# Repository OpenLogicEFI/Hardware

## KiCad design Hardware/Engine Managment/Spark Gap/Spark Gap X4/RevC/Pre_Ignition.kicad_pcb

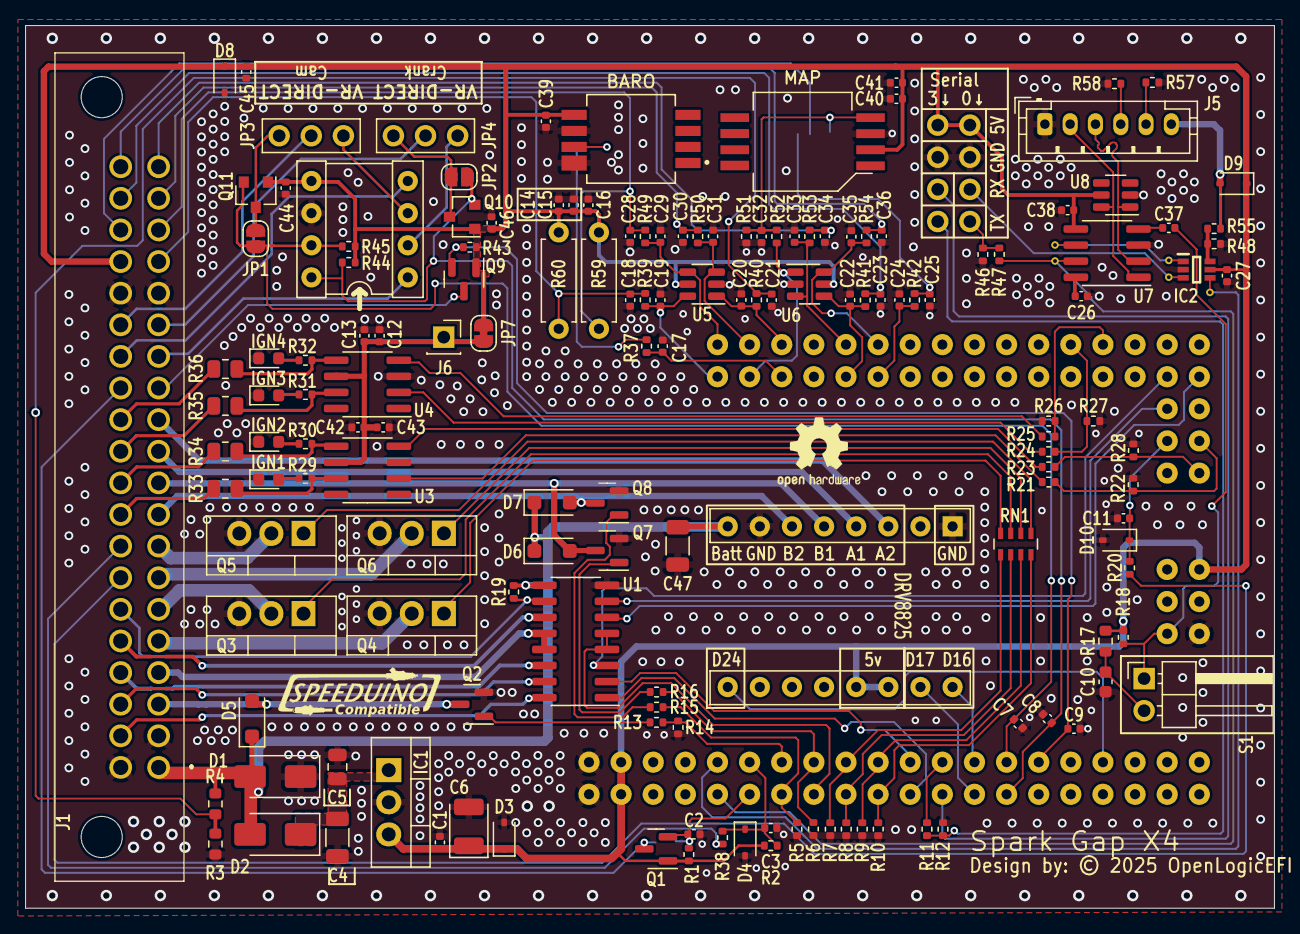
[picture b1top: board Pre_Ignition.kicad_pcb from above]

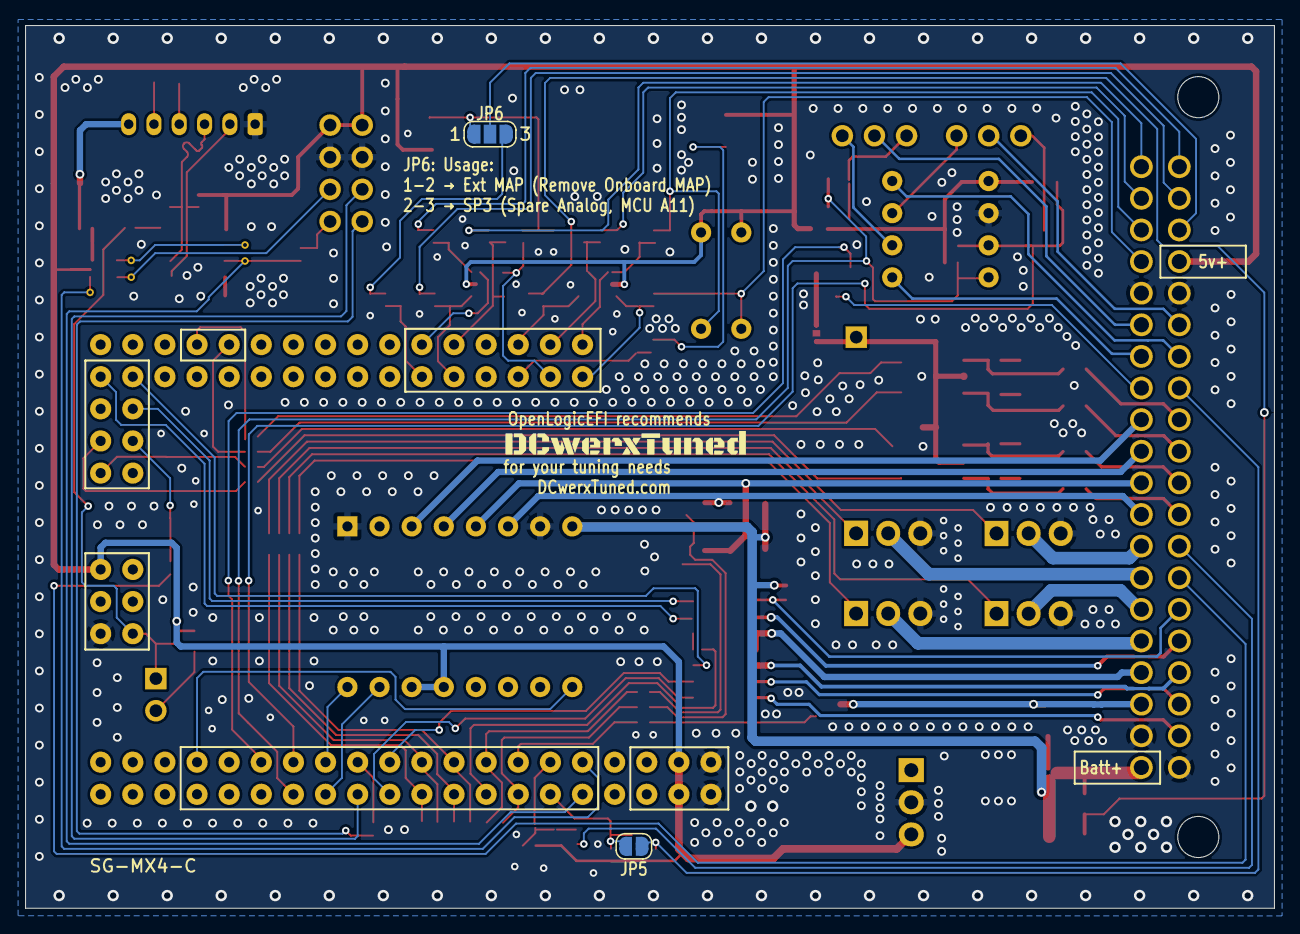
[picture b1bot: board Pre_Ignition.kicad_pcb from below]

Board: 2 copper layers, 98.8 x 69.8 mm, 166 parts (2 on the bottom side), 120 nets.

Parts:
A1: DRV8825_Module; DVR8825-Labeled-Front
C1, C7, C12, C14, C17, C18, C21, C23, C25, C26, C27, C28, C30, C34, C36, C37, C38, C39, C40, C43, C44, C45, C46: 100nF; C_0402_1005Metric
C2, C8, C9: 10nF; C_0402_1005Metric
C3, C11, C15, C19, C20, C22, C24, C29, C31, C33, C35: 220nF; C_0402_1005Metric
C4, C47: 10uF; C_1206_3216Metric
C5: 470nF; C_0805_2012Metric
C6: 100uF; CP_EIA-3528-15_AVX-H
C10: 10uF; C_0603_1608Metric
C13, C16, C41, C42: 1uF; C_0402_1005Metric
C32: 47pF; C_0402_1005Metric
D1: SMAJ18CA; D_SMA
D2: SS34; D_SMA
D3, D4, D8, D10: 5.6v; D_SOD-323
D5, D6, D7: DSK210; D_SOD-123F
D9: 1N5819WS; D_SOD-323
G1: Logo_Open_Hardware_Small; SpeeduinoCompatible-14mm
G2: Logo_Open_Hardware_Small; OSHW-Logo2_7.3x6mm_SilkScreen
IC1: 7805; TO-220-3_Vertical_SmallCrtYrd
IC2: 74LVC1G157GW,125; SOP65P210X110-6N
IC3: KP234XTMA1; KP234-Handsoldering
IC4: MPXHZ6400; MPXHxxx_Handsoldering
IGN1, IGN2, IGN3, IGN4: LED; LED_0603_1608Metric
J1: MX23A40NF1
J2: VR_Header; Socket_VRConditioner_Corrected
J3, J4: Conn_01x04; 1X4-PROTO-NoSilk
J5: USB-S0; JST_PH_B6B-PH-K_1x06_P2.00mm_Vertical
J6: Conn_01x01; PinSocket_1x01_P2.54mm_Vertical
JP1, JP2, JP5: FET Bypass; SolderJumper-2_P1.3mm_Open_RoundedPad1.0x1.5mm
JP3, JP4: DIRECT/VR; 1x03-Proto
JP6: SolderJumper_3_Open; SolderJumper-3-OPEN
JP7: Conn_01x02; SolderJumper-2_P1.3mm_Bridged_RoundedPad1.0x1.5mm
Q1, Q2, Q7, Q8, Q9, Q10, Q11: AO3400A; SOT-23
Q3, Q4, Q5, Q6: STP75N04Z; TO-220-3_Vertical
R1, R11, R20, R21, R23, R24, R25, R43, R44, R45, R47: 1k; R_0402_1005Metric
R2: 2.2k; R_0402_1005Metric
R3: 1k; R_0603_1608Metric
R4: 3.9k; R_0603_1608Metric
R5, R6, R7, R8, R9, R10, R14, R22, R26, R27, R28: 100k; R_0402_1005Metric
R12, R46: 2k; R_0402_1005Metric
R13, R15, R16, R29, R30, R31, R32, R38, R39, R40, R41, R42, R49, R50, R52, R53, R54, R55: 470r; R_0402_1005Metric
R17: 120r; R_0603_1608Metric
R18, R19, R48: 10k; R_0402_1005Metric
R33, R34, R35, R36: 22; R_0805_2012Metric
R37, R51: 51k; R_0402_1005Metric
R57, R58: 5.1k; R_0402_1005Metric
R59, R60: 2.49k; R_Axial_DIN0207_L6.3mm_D2.5mm_P7.62mm_Horizontal
RN1: RN_1k; R_Array_Concave_4x0603
S1: Reset Control; PinHeader_1x02_P2.54mm_Horizontal
TP1, TP2, TP3, TP4, TP5: TestPoint; TestPoint_THT_D0.6mm_Drill0.3mm
U1: ULN2003ADR; SOIC-16_3.9x9.9mm_P1.27mm
U2: Mega_Pro_VinPinsUnpopulated; Arduino_Mega_Mini_2560_SmallCrtYd_NoVin
U3, U4: TC4424; SOIC-8_3.9x4.9mm_P1.27mm
U5, U6, U8: SRV05-4; SOT-23-6
U7: CH340N; SOIC-8_3.9x4.9mm_P1.27mm

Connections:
+5V: A1.13 (~RST), A1.14 (~SLP), C1.1, C6.1, C14.1, C15.1, C16.1, C27.2, C38.1, C39.1, C40.1, C41.1, C44.1, C45.1, C46.1, D3.1 (K), D8.1 (K), D9.1 (K), IC1.3 (OUT), IC2.5 (VCC), IC3.5 (VDD), IC4.2 (VS), J1.37, J2.5, J3.1, J4.1, JP7.2 (B), Q1.1 (G), Q9.1 (G), Q10.1 (G), Q11.1 (G), R1.1, R2.2, R17.2, R18.1, R43.1, R44.1, R45.1, R59.1, R60.2, U2.5V_1 (5V), U2.5V_2 (5V), U2.5V_3 (5V), U5.5 (REF), U6.5 (REF), U7.5 (VCC), U8.5 (REF)
+BATT: A1.8 (VMOT), C47.1, D1.2 (A2), D2.2 (A), D5.1 (K), D6.1 (K), D7.1 (K), J1.1, R4.2, R19.2, U1.9 (COM)
+VSW: C12.1, C13.1, C42.1, C43.1, J6.1, JP7.1 (A), U3.6 (V+), U4.6 (V+)
/MCU and Power/Batt_Protected: C4.1, C5.1, D2.1 (K), IC1.1 (IN)
ADC1: C23.1, J1.39, R41.2
ADC2: C36.1, J1.40, R54.2
ADC3: C25.1, JP6.3 (B), R42.2
BOOST: J1.4, U1.12 (O5), U1.13 (O4)
BaroIn: IC3.7 (VOUT), R37.1
CH340-TX0: IC2.1 (I1), TP4.1, TP5.1, U7.6 (RXD)
CLT: C18.1, J1.17, R39.2, R60.1
Cam2: J1.33, JP5.1 (A), Q1.3 (D)
Cam-In: J1.35, JP3.2
Clutch: J1.27, R20.2
Crank-In: J1.15, JP4.2
D12-OUT: J1.23, U1.15 (O2)
D13-OUT: J1.22, U1.16 (O1)
D+: J5.2, U7.1 (UD+), U8.6 (I/O_4)
D-: J5.3, U7.2 (UD-), U8.1 (I/O_1)
Fan: J1.25, U1.11 (O6)
Flex: J1.28, R38.2
Fuel-Pump: J1.24, U1.14 (O3)
GND: A1.1 (GND), A1.7 (GND), C1.2, C2.1, C3.2, C4.2, C5.2, C6.2, C7.1, C8.1, C9.2, C10.2, C11.2, C12.2, C13.2, C14.2, C15.2, C16.2, C17.2, C18.2, C19.2, C20.2, C21.2, C22.2, C23.2, C24.2, C25.2, C26.2, C27.1, C28.2, C29.2, C30.2, C31.2, C32.2, C33.2, C34.2, C35.2, C36.2, C38.2, C39.2, C40.2, C41.2, C42.2, C43.2, C44.2, C45.2, C46.2, C47.2, D1.1 (A1), D3.2 (A), D4.2 (A), D8.2 (A), D10.2 (A), IC1.2 (GND), IC2.2 (GND), IC3.6 (GND), IC3.8 (GND), IC4.3 (GND), IGN1.1 (K), IGN2.1 (K), IGN3.1 (K), IGN4.1 (K), J1.2, J1.16, J1.21, J1.36, J2.6, J3.2, J4.2, J5.1, Q2.2 (S), Q3.3 (S), Q4.3 (S), Q5.3 (S), Q6.3 (S), Q7.2 (S), Q8.2 (S), R3.1, R5.1, R6.1, R7.1, R8.1, R9.1, R10.1, R12.2, R14.1, R22.1, R26.1, R27.1, R28.1, R46.2, R48.1, R51.1, R57.2, R58.2, U1.8 (GND), U2.GND_1 (GND), U2.GND_2 (GND), U2.GND_3 (GND), U3.3 (GND), U4.3 (GND), U5.2 (GND), U6.2 (GND), U7.3 (GND), U8.2 (GND)
IAT: C28.1, J1.18, R49.2, R59.2
IDLE1: A1.6 (B2), D7.2 (A), J1.9, Q8.3 (D)
IDLE2: A1.5 (B1), D6.2 (A), J1.10, Q7.3 (D)
IGN1: J1.32, R36.1
IGN2: J1.31, R35.1
IGN3: J1.30, R34.1
IGN4: J1.29, R33.1
INJ1: J1.5, Q4.2 (D)
INJ2: J1.6, Q3.2 (D)
INJ3: J1.7, Q6.2 (D)
INJ4: J1.8, Q5.2 (D)
MC-A0: C29.1, R49.1, U2.A0, U5.4 (I/O_3)
MC-A1: C19.1, R39.1, U2.A1, U5.6 (I/O_4)
MC-A2: C31.1, R50.1, U2.A2, U5.3 (I/O_2)
MC-A3: R52.2, U2.A3, U6.1 (I/O_1)
MC-A4: C20.1, R40.1, U2.A4, U5.1 (I/O_1)
MC-A5: C17.1, R37.2, U2.A5
MC-A8: C33.1, R53.1, U2.A8, U6.3 (I/O_2)
MC-A9: C22.1, R41.1, U2.A9, U6.4 (I/O_3)
MC-A10: C35.1, R54.1, U2.A10, U6.6 (I/O_4)
MC-A11: C24.1, R42.1, U2.A11
MC-D2: C3.1, D4.1 (K), R2.1, R38.1, U2.D2
MC-D3: C2.2, JP5.2 (B), Q1.2 (S), R1.2, U2.D3
MC-D4: R13.1, R14.2, U2.D4
MC-D5: R5.2, R15.1, U2.D5
MC-D6: R6.2, R16.1, U2.D6
MC-D7: U1.4 (I4), U1.5 (I5), U2.D7
MC-D8: R7.2, RN1.5 (R4.2), U2.D8
MC-D9: R8.2, RN1.6 (R3.2), U2.D9
MC-D10: R9.2, RN1.7 (R2.2), U2.D10
MC-D11: R10.2, RN1.8 (R1.2), U2.D11
MC-D12: U1.2 (I2), U2.D12
MC-D13: U1.1 (I1), U2.D13
MC-D14-TX3: R11.1, U2.D14
MC-D15-RX3: J3.3, U2.D15
MC-D16: A1.16 (DIR), U2.D16
MC-D17: A1.15 (STEP), U2.D17
MC-D18: C7.2, J2.7, JP1.2 (B), Q11.2 (S), R45.2, U2.D18
MC-D19: C8.2, J2.8, JP2.2 (B), Q10.2 (S), R44.2, U2.D19
MC-D20: C9.1, Q9.2 (S), R43.2, U2.D20
MC-D24: A1.9 (~EN), U2.D24
MC-D38: R24.1, R27.2, U2.D38
MC-D40: R25.1, R26.2, U2.D40
MC-D45: U1.3 (I3), U2.D45
MC-D47: U1.6 (I6), U2.D47
MC-D49: U1.7 (I7), U2.D49
MC-D50: R21.1, R22.2, U2.D50
MC-D51: C11.1, D10.1 (K), R20.1, U2.D51
MC-D52: R23.1, R28.2, U2.D52
MC-RESET: C37.2, R18.2, S1.1, U2.RESET
MC-RX0: IC2.4 (Y), TP1.1, U2.RX
MC-TX0: R47.1, TP3.1, U2.TX, U7.7 (TXD)
Map-Ext: J1.38, JP6.2 (C)
MapIn: C32.1, IC4.4 (VOUT), JP6.1 (A), R51.2, R52.1
unnamed: C21.1, R3.2, R4.1, R40.2
unnamed: IC2.6 (S), R48.2, R55.1
unnamed: IGN1.2 (A), R29.2
unnamed: IGN2.2 (A), R30.2
unnamed: IGN3.2 (A), R31.2
unnamed: IGN4.2 (A), R32.2
unnamed: J3.4, R11.2, R12.1
unnamed: J4.4, R46.1, R47.2
unnamed: J5.4, R58.1
unnamed: J5.5, R57.1
unnamed: JP1.1 (A), JP3.1, Q11.3 (D)
unnamed: JP2.1 (A), JP4.1, Q10.3 (D)
unnamed: Q2.1 (G), R13.2
unnamed: Q3.1 (G), RN1.3 (R3.1)
unnamed: Q4.1 (G), RN1.4 (R4.1)
unnamed: Q5.1 (G), RN1.1 (R1.1)
unnamed: Q6.1 (G), RN1.2 (R2.1)
unnamed: Q7.1 (G), R16.2
unnamed: Q8.1 (G), R15.2
unnamed: C10.1, R17.1, S1.2
unnamed: R21.2, U3.2 (IN_A)
unnamed: R23.2, U3.4 (IN_B)
unnamed: R29.1, R33.2, U3.7 (OUT_A)
unnamed: R30.1, R34.2, U3.5 (OUT_B)
unnamed: R24.2, U4.2 (IN_A)
unnamed: R25.2, U4.4 (IN_B)
unnamed: R31.1, R35.2, U4.7 (OUT_A)
unnamed: R32.1, R36.2, U4.5 (OUT_B)
unnamed: C26.1, U7.8 (V3)
unnamed: C37.1, U7.4 (~RTS)
O2: C34.1, J1.20, R53.2
S0-TX-Proto: IC2.3 (I0), J4.3, TP2.1
Step-A1: A1.4 (A1), J1.11
Step-A2: A1.3 (A2), J1.12
TPS: C30.1, J1.19, R50.2
Tach: J1.26, R19.1, U1.10 (O7)
VBus: D9.2 (A), J5.6, R55.2
VR1+: J2.2, JP4.3
VR1-: J1.14, J2.1
VR2+: J2.3, JP3.3
VR2-: J1.34, J2.4
VSS: J1.13, Q9.3 (D)
VVT: D5.2 (A), J1.3, Q2.3 (D)

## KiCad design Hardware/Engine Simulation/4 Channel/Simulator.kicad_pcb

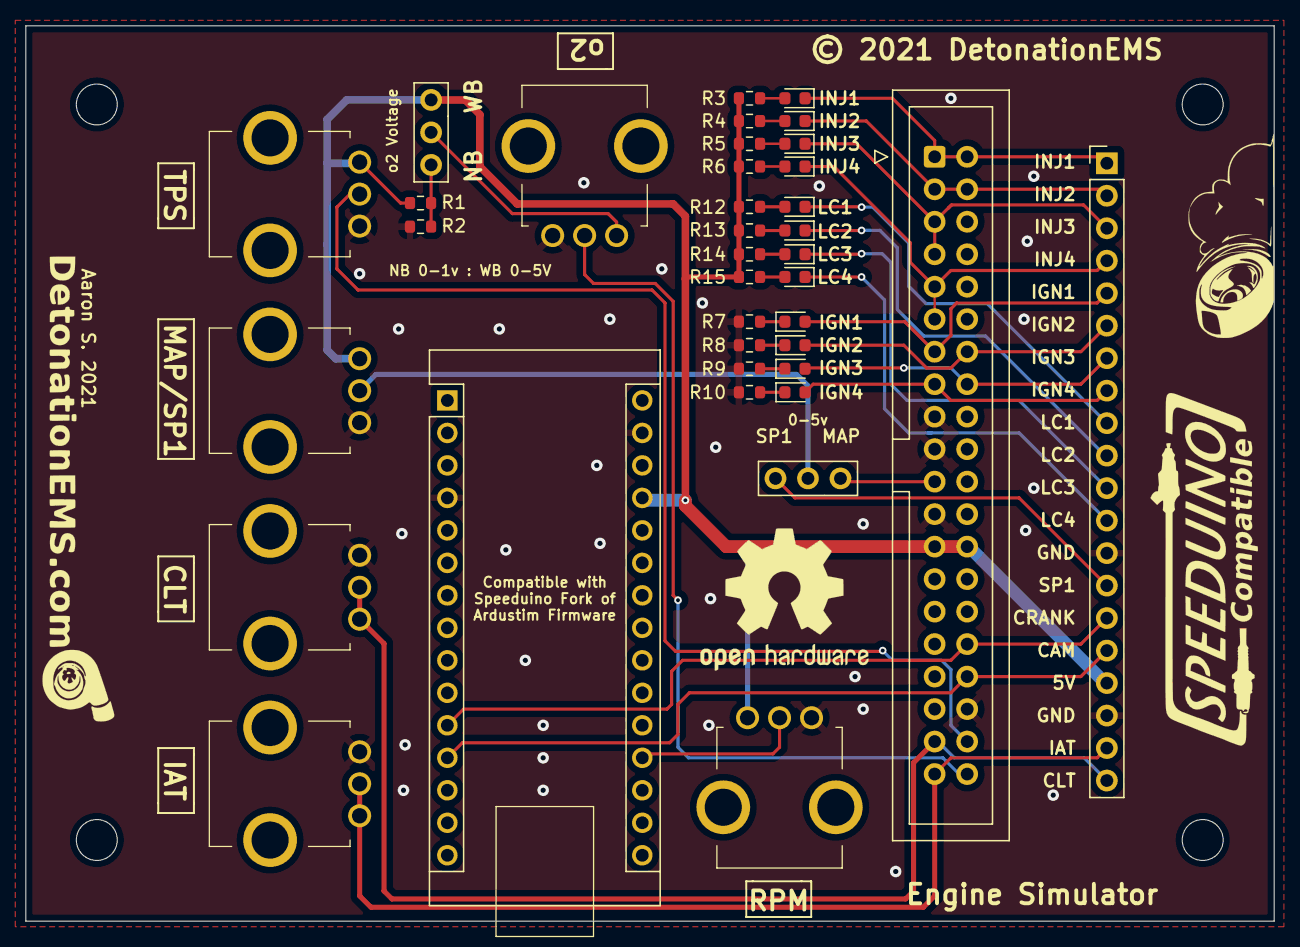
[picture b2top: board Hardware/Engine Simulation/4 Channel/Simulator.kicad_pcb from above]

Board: 2 copper layers, 97.6 x 70.0 mm, 45 parts (0 on the bottom side), 38 nets.

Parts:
A1: Arduino_Nano_v3.x; Arduino_Nano
G1: Logo_Open_Hardware_Small; TireSmoke-22mm
G2: Logo_Open_Hardware_Small; DetonationEMS
G3: Logo_Open_Hardware_Small; SpeeduinoCompatible-30mm
G4: Logo_Open_Hardware_Small; OSHW-Logo2_14.6x12mm_SilkScreen
H1, H2, H3, H4: MountingHole; MountingHole_3.2mm_M3
J1, J8: Conn_01x03; 3-PinSwitch
J2: Conn_02x20_Counter_Clockwise; IDC-Header_2x20_P2.54mm_Vertical_Speeduino
J6: Header; PinHeader_1x20_P2.54mm_Vertical
LED1: INJ1; LED_0603_1608Metric
LED2: INJ2; LED_0603_1608Metric
LED3: INJ3; LED_0603_1608Metric
LED4: INJ4; LED_0603_1608Metric
LED5: IGN1; LED_0603_1608Metric
LED6: IGN2; LED_0603_1608Metric
LED7: IGN3; LED_0603_1608Metric
LED8: IGN4; LED_0603_1608Metric
LED10: IDLE; LED_0603_1608Metric
LED11: IDLE2; LED_0603_1608Metric
LED12: VVT; LED_0603_1608Metric
LED13: BOOST; LED_0603_1608Metric
POT1: IAT; RV09AF4020KB10K
POT2: CLT; RV09AF4020KB10K
POT3: TPS; RV09AF4020KB10K
POT4: MAP/SP1; RV09AF4020KB10K
POT5: o2; RV09AF4020KB10K
POT6: RPM; RV09AF4020KB10K
R1: 470; R_0603_1608Metric
R2: 100; R_0603_1608Metric
R3, R4, R5, R6, R7, R8, R9, R10, R12, R13, R14, R15: 330; R_0603_1608Metric

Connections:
+5V: A1.27 (+5V), J1.1, J2.13, J2.28, J6.17, POT3.3, POT4.3, POT6.3, R1.1, R3.1, R4.1, R5.1, R6.1, R12.1, R13.1, R14.1, R15.1
CAM: A1.12 (D9), J2.24, J6.16
CLT: J2.19, J6.20, POT2.1, POT2.2
CRANK: A1.11 (D8), J2.25, J6.15
GND: A1.4 (GND), A1.29 (GND), J2.9, J2.10, J2.12, J2.23, J6.13, J6.18, POT1.3, POT2.3, POT3.1, POT4.1, POT5.1, POT6.1, R2.2, R7.1, R8.1, R9.1, R10.1
IAT: J2.20, J6.19, POT1.1, POT1.2
IGN1: J2.7, J6.5, LED5.2 (A)
IGN2: J2.34, J6.6, LED6.2 (A)
IGN3: J2.33, J6.7, LED7.2 (A)
IGN4: J2.8, J6.8, LED8.2 (A)
INJ1: J2.1, J2.40, J6.1, LED1.1 (K)
INJ2: J2.2, J2.39, J6.2, LED2.1 (K)
INJ3: J2.3, J2.4, J6.3, LED3.1 (K)
INJ4: J2.5, J2.6, J6.4, LED4.1 (K)
LC1: J6.9, LED10.1 (K)
LC2: J6.10, LED11.1 (K)
LC3: J6.11, LED12.1 (K)
LC4: J6.12, LED13.1 (K)
MAP: J2.11, J8.1
MC-A0: A1.19 (A0), POT6.2
unnamed: J1.3, R1.2, R2.1
unnamed: LED1.2 (A), R3.2
unnamed: LED2.2 (A), R4.2
unnamed: LED3.2 (A), R5.2
unnamed: LED4.2 (A), R6.2
unnamed: LED5.1 (K), R7.2
unnamed: LED6.1 (K), R8.2
unnamed: LED7.1 (K), R9.2
unnamed: LED8.1 (K), R10.2
unnamed: LED10.2 (A), R12.2
unnamed: LED11.2 (A), R13.2
unnamed: LED12.2 (A), R14.2
unnamed: LED13.2 (A), R15.2
RV4: J8.2, POT4.2
SP1: J6.14, J8.3
TPS: J2.22, POT3.2
o2: J2.21, POT5.2
o2-Voltage: J1.2, POT5.3

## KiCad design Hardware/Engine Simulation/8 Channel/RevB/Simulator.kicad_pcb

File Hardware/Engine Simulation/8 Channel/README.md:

# Engine Simulator

www.openlogicefi.com

Engine Simulator for Speeduino fork of Ardustim - https://github.com/speeduino/Ardu-Stim

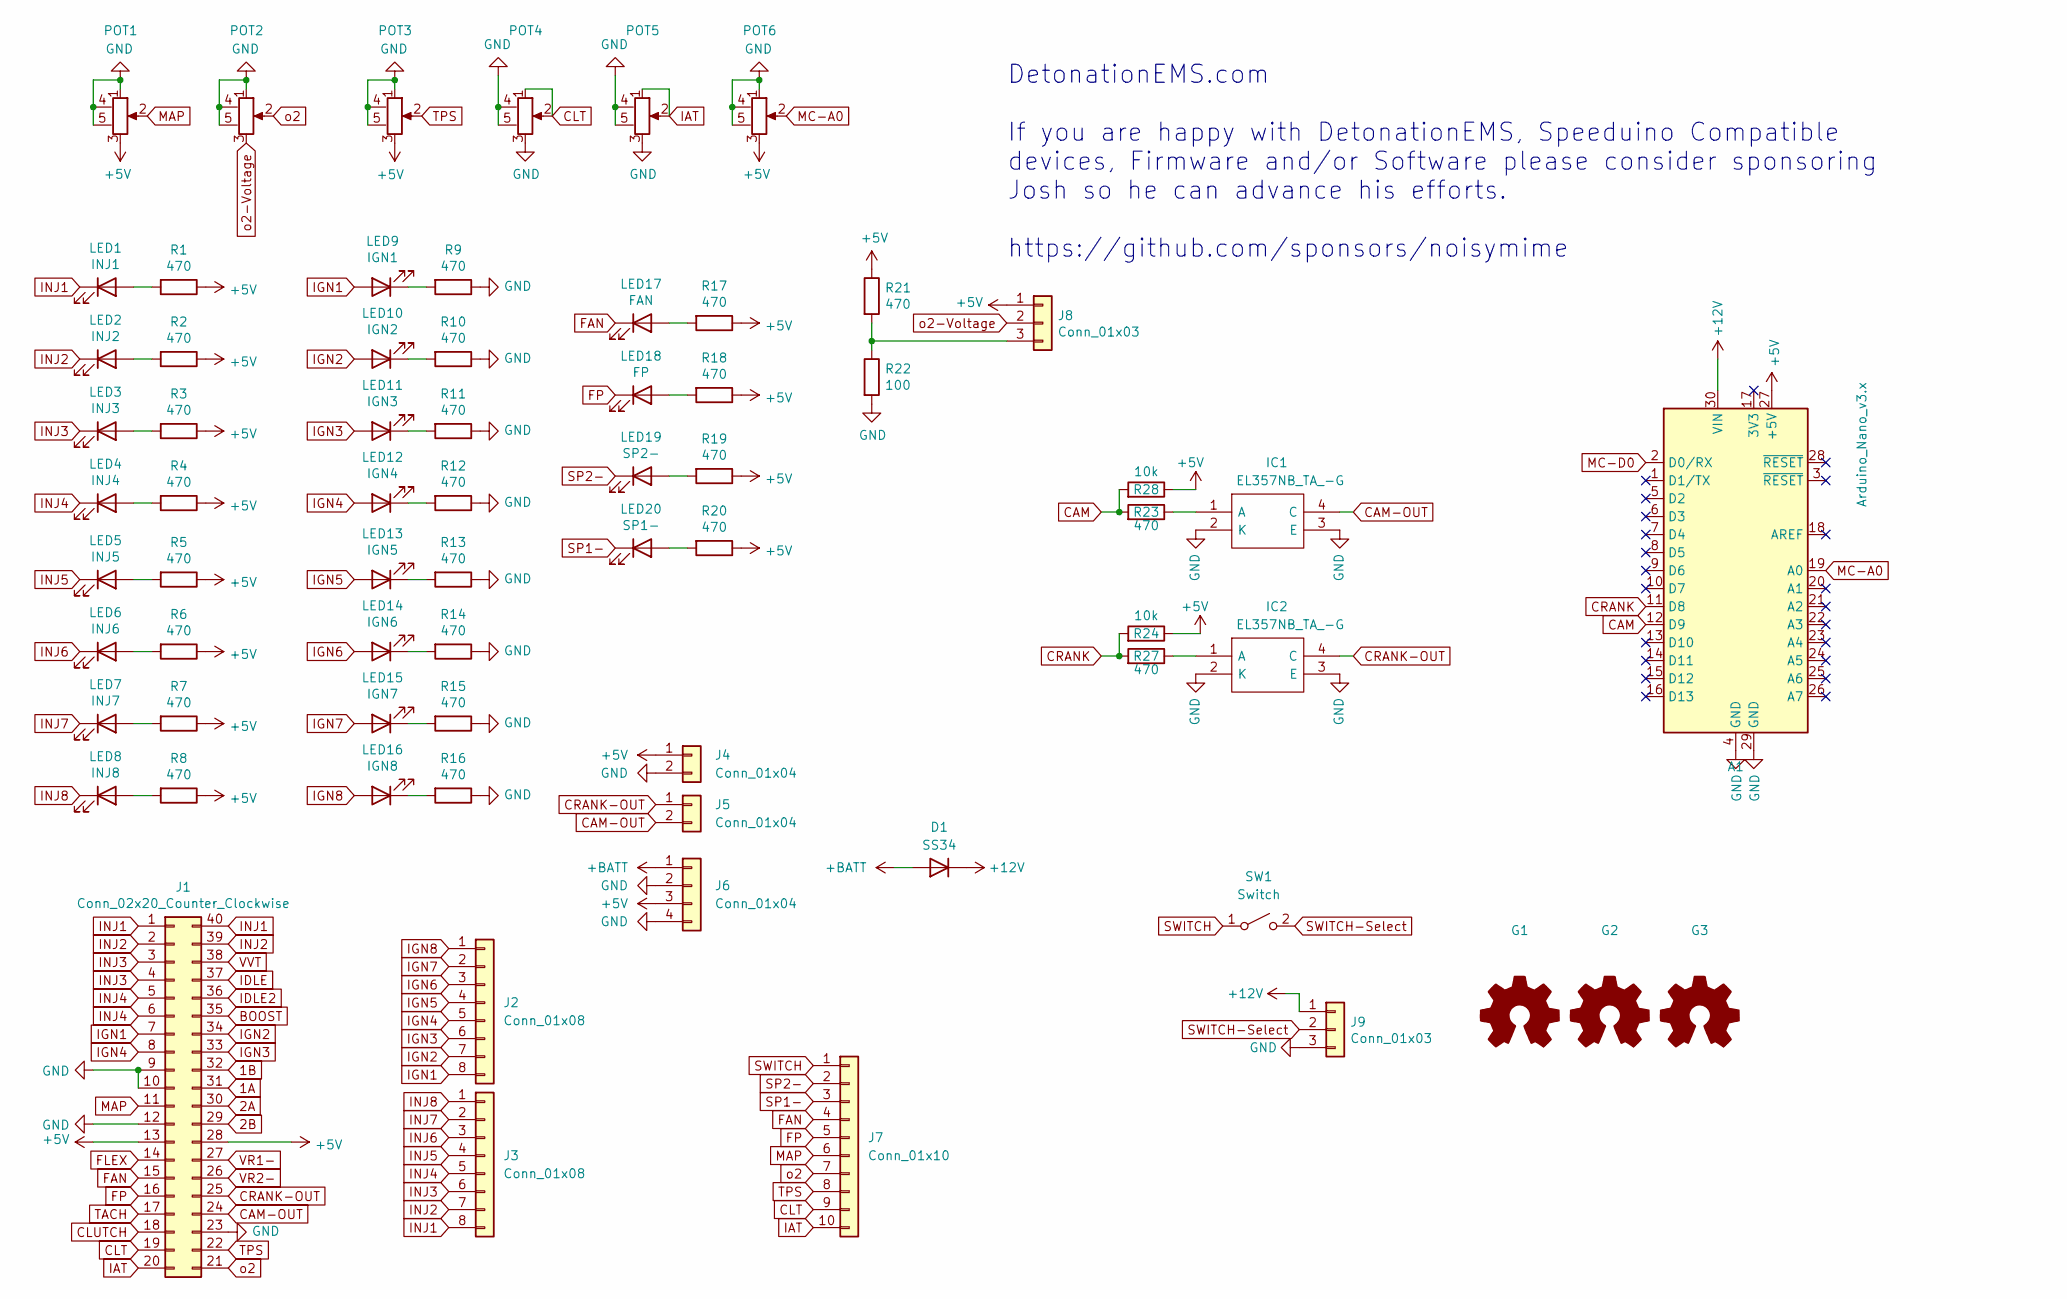
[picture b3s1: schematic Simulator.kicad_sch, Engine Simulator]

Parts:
A1: Arduino_Nano_v3.x; Arduino_Nano
D1: SS34; D_SOD-123; LCSC C8598
G1: Logo_Open_Hardware_Small; Design by 30mm
G2: Logo_Open_Hardware_Small; SpeeduinoCompatible-17mm
G3: Logo_Open_Hardware_Small; OSHW-Logo2_7.3x6mm_SilkScreen
IC1, IC2: EL357NB_TA_-G; SOP254P700X200-4N; Manufacturer_Part_Number EL357NB(TA)-G; Mouser Part Number 638-EL357NBTAG
J1: Conn_02x20_Counter_Clockwise; IDC-Header_2x20_P2.54mm_Vertical_Speeduino
J2, J3: Conn_01x08; TerminalBlock_Phoenix_PT-1,5-8-3.5-H_1x08_P3.50mm_Horizontal
J4, J5: Conn_01x04; TerminalBlock_Phoenix_PT-1,5-2-3.5-H_1x02_P3.50mm_Horizontal
J6: Conn_01x04; TerminalBlock_Phoenix_PT-1,5-4-3.5-H_1x04_P3.50mm_Horizontal
J7: Conn_01x10; TerminalBlock_Phoenix_PT-1,5-10-3.5-H_1x10_P3.50mm_Horizont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
J8, J9: Conn_01x03; 3-PinSwitch
LED1: INJ1; LED_0603_1608Metric; LCSC C2286
LED2: INJ2; LED_0603_1608Metric; LCSC C2286
LED3: INJ3; LED_0603_1608Metric; LCSC C2286
LED4: INJ4; LED_0603_1608Metric; LCSC C2286
LED5: INJ5; LED_0603_1608Metric; LCSC C2286
LED6: INJ6; LED_0603_1608Metric; LCSC C2286
LED7: INJ7; LED_0603_1608Metric; LCSC C2286
LED8: INJ8; LED_0603_1608Metric; LCSC C2286
LED9: IGN1; LED_0603_1608Metric; LCSC C2286
LED10: IGN2; LED_0603_1608Metric; LCSC C2286
LED11: IGN3; LED_0603_1608Metric; LCSC C2286
LED12: IGN4; LED_0603_1608Metric; LCSC C2286
LED13: IGN5; LED_0603_1608Metric; LCSC C2286
LED14: IGN6; LED_0603_1608Metric; LCSC C2286
LED15: IGN7; LED_0603_1608Metric; LCSC C2286
LED16: IGN8; LED_0603_1608Metric; LCSC C2286
LED17: FAN; LED_0603_1608Metric; LCSC C2286
LED18: FP; LED_0603_1608Metric; LCSC C2286
LED19: SP2-; LED_0603_1608Metric; LCSC C2286
LED20: SP1-; LED_0603_1608Metric; LCSC C2286
POT1: IAT; RV09AF4020KB10K
POT2: CLT; RV09AF4020KB10K
POT3: MAP/SP1; RV09AF4020KB10K
POT4: TPS; RV09AF4020KB10K
POT5: o2; RV09AF4020KB10K
POT6: RPM; RV09AF4020KB10K
R1, R2, R3, R4, R5, R6, R7, R8, R9, R10, R11, R12, R13, R14, R15, R16, R17, R18, R19, R20, R21, R23, R27: 470; R_0603_1608Metric; LCSC C23179
R22: 100; R_0603_1608Metric; LCSC C22775
R24, R28: 10k; R_0603_1608Metric; LCSC C23138
SW1: Switch; SW_PUSH_6mm_H9.5mm

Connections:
1A: J1.31
1B: J1.32
2A: J1.30
2B: J1.29
+5V: A1.27 (+5V), J1.13, J1.28, J4.1, J6.3, J8.1, POT1.3, POT3.3, POT6.3, R1.1, R2.1, R3.1, R4.1, R5.1, R6.1, R7.1, R8.1, R17.1, R18.1, R19.1, R20.1, R21.1, R24.1, R28.1
+12V: A1.30 (VIN), D1.1 (K), J9.1
+BATT: D1.2 (A), J6.1
BOOST: J1.35
CAM: A1.12 (D9), R23.2, R28.2
CAM-OUT: IC1.4 (C), J1.24, J5.2
CLT: J1.19, J7.9, POT4.1, POT4.2
CLUTCH: J1.18
CRANK: A1.11 (D8), R24.2, R27.2
CRANK-OUT: IC2.4 (C), J1.25, J5.1
FAN: J1.15, J7.4, LED17.1 (K)
FLEX: J1.14
FP: J1.16, J7.5, LED18.1 (K)
GND: A1.4 (GND), A1.29 (GND), IC1.2 (K), IC1.3 (E), IC2.2 (K), IC2.3 (E), J1.9, J1.10, J1.12, J1.23, J4.2, J6.2, J6.4, J9.3, POT1.1, POT1.4 (Mounting_Tap), POT1.5 (Mounting_Tap), POT2.1, POT2.4 (Mounting_Tap), POT2.5 (Mounting_Tap), POT3.1, POT3.4 (Mounting_Tap), POT3.5 (Mounting_Tap), POT4.3, POT4.4 (Mounting_Tap), POT4.5 (Mounting_Tap), POT5.3, POT5.4 (Mounting_Tap), POT5.5 (Mounting_Tap), POT6.1, POT6.4 (Mounting_Tap), POT6.5 (Mounting_Tap), R9.1, R10.1, R11.1, R12.1, R13.1, R14.1, R15.1, R16.1, R22.2; also elsewhere on the board
IAT: J1.20, J7.10, POT5.1, POT5.2
IDLE: J1.37
IDLE2: J1.36
IGN1: J1.7, J2.8, LED9.2 (A)
IGN2: J1.34, J2.7, LED10.2 (A)
IGN3: J1.33, J2.6, LED11.2 (A)
IGN4: J1.8, J2.5, LED12.2 (A)
IGN5: J2.4, LED13.2 (A)
IGN6: J2.3, LED14.2 (A)
IGN7: J2.2, LED15.2 (A)
IGN8: J2.1, LED16.2 (A)
INJ1: J1.1, J1.40, J3.8, LED1.1 (K)
INJ2: J1.2, J1.39, J3.7, LED2.1 (K)
INJ3: J1.3, J1.4, J3.6, LED3.1 (K)
INJ4: J1.5, J1.6, J3.5, LED4.1 (K)
INJ5: J3.4, LED5.1 (K)
INJ6: J3.3, LED6.1 (K)
INJ7: J3.2, LED7.1 (K)
INJ8: J3.1, LED8.1 (K)
MAP: J1.11, J7.6, POT1.2
MC-A0: A1.19 (A0), POT6.2
MC-D0: A1.2 (D0/RX)
unnamed: J8.3, R21.2, R22.1
unnamed: LED1.2 (A), R1.2
unnamed: LED2.2 (A), R2.2
unnamed: LED3.2 (A), R3.2
unnamed: LED4.2 (A), R4.2
unnamed: LED5.2 (A), R5.2
unnamed: LED6.2 (A), R6.2
unnamed: LED7.2 (A), R7.2
unnamed: LED8.2 (A), R8.2
unnamed: LED9.1 (K), R9.2
unnamed: LED10.1 (K), R10.2
unnamed: LED11.1 (K), R11.2
unnamed: LED12.1 (K), R12.2
unnamed: LED13.1 (K), R13.2
unnamed: LED14.1 (K), R14.2
unnamed: LED15.1 (K), R15.2
unnamed 56: LED16.1 (K), R16.2; also elsewhere on the board
unnamed: LED17.2 (A), R17.2
unnamed: LED18.2 (A), R18.2
unnamed: LED19.2 (A), R19.2
unnamed: LED20.2 (A), R20.2
unnamed: IC1.1 (A), R23.1
unnamed: IC2.1 (A), R27.1
SP1-: J7.3, LED20.1 (K)
SP2-: J7.2, LED19.1 (K)
SWITCH: J7.1, SW1.1 (A)
SWITCH-Select: J9.2, SW1.2 (B)
TACH: J1.17
TPS: J1.22, J7.8, POT3.2
VR1-: J1.27
VR2-: J1.26
VVT: J1.38
o2: J1.21, J7.7, POT2.2
o2-Voltage: J8.2, POT2.3

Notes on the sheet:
DetonationEMS.com If you are happy with DetonationEMS, Speeduino Compatible devices, Firmware and/or Software please consider sponsoring Josh so he can advance his efforts. https://github.com/sponsors/noisymime

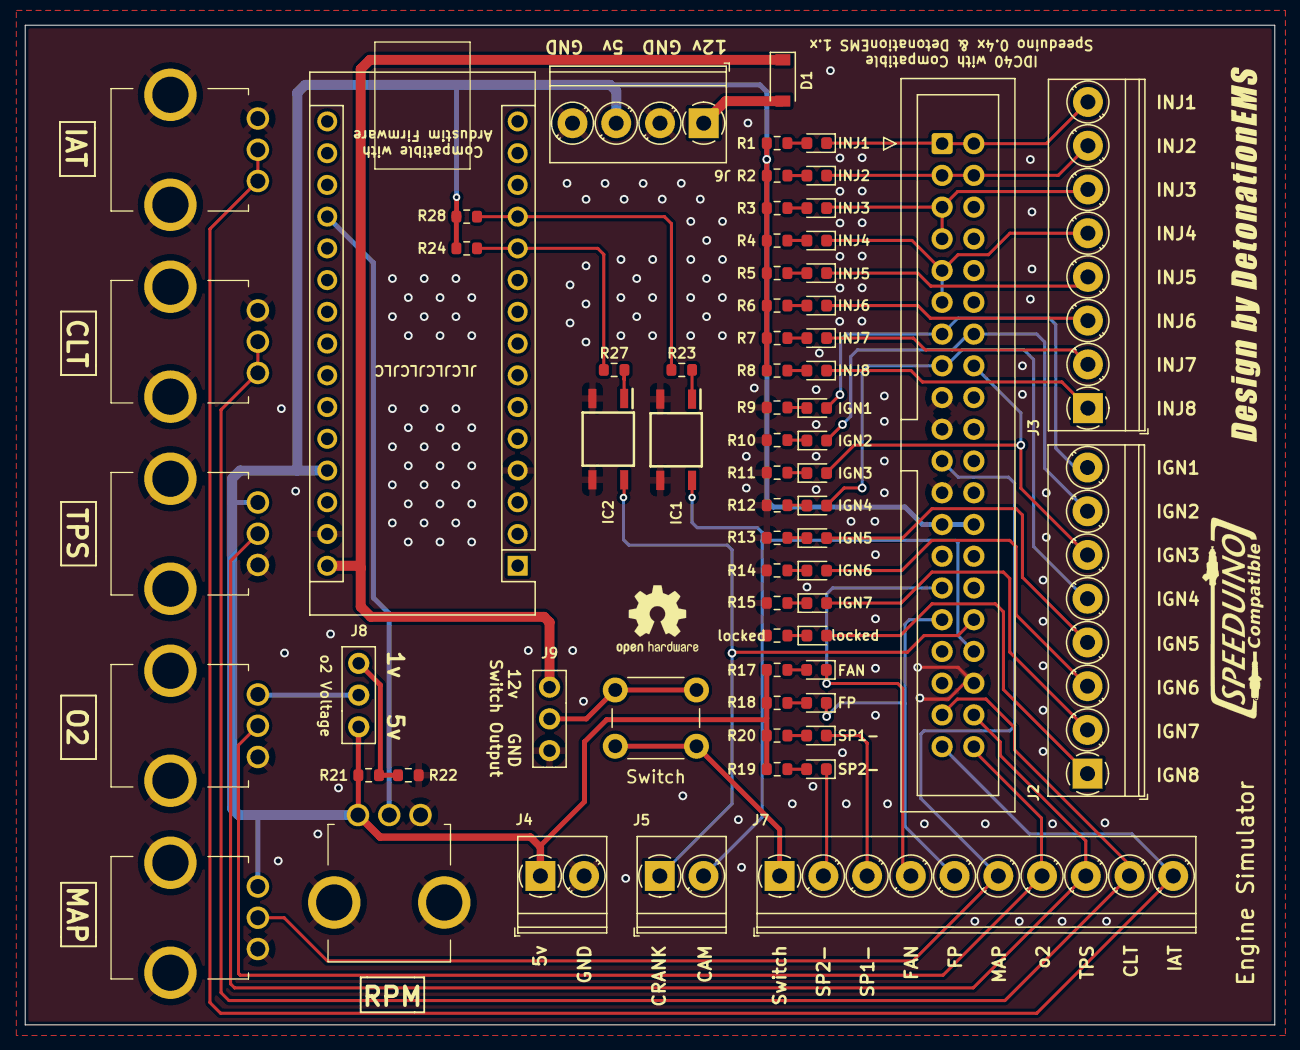
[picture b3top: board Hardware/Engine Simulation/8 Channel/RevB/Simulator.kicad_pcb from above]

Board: 2 copper layers, 100.0 x 80.0 mm, 69 parts (0 on the bottom side), 60 nets.

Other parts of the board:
locked: 470; R_0603_1608Metric

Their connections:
GND: locked.1; also elsewhere on the board
unnamed 56: locked.2; also elsewhere on the board

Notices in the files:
Hardware/Engine Managment/Spark Gap/Spark Gap X4/RevC/Pre_Ignition.kicad_pcb:
Design by: © 2025 OpenLogicEFI
Hardware/Engine Simulation/4 Channel/Simulator.kicad_pcb:
© 2021 DetonationEMS
Hardware/Engine Simulation/8 Channel/RevB/Simulator.kicad_pcb:
DetonationEMS © 2022
Hardware/Engine Simulation/8 Channel/RevC/Simulator.kicad_pcb:
DetonationEMS © 2023 (Aaron S.)
Hardware/Modules/MAP Sensor Modules/PMAP-L/map-pinned.kicad_sch:
© 2023 DetonationEMS (Aaron S.)
Hardware/Modules/MAP Sensor Modules/PMAP-M/map-pinned.kicad_pcb:
©OpenLogicEFI 2025
